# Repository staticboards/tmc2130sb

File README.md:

# TMC2130 SB

The TM2130 SB is a stepper motor driver based on the advanced TMC 2130 driver.

The TMC2130 SB is a derived work from the Silent Step Stick https://github.com/watterott/SilentStepStick. We rewrote the project using kicad, with some improvements, like the potentiometer on the upper side. This is a 4 layer board with improved heat dissipation.

* Full compatible with Pololu a4988 and DRV8825
* Compatible with SPI mode

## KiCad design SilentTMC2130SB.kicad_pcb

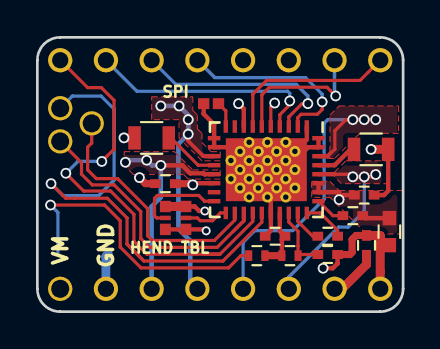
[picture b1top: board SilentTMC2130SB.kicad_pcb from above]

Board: 4 copper layers, 20.3 x 15.2 mm, 22 parts (1 on the bottom side), 28 nets.

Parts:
C1, C4, C5, C7: 100n/50V; C_0402
C2: 470n/10V; C_0402
C3: 4u7/10V; C_0402
C6: 22n/50V; C_0402
C8: 1u/50V; C_0603
J1: HEND; JUMPER3-SMD
J2: TBL; JUMPER3-SMD
J3: SPI; JUMPER_SMD
J4, J5: CONN_01X08; Pin_Header_Straight_1x08_Pitch2.54mm
J6, J7, J8: CONN_01X01; Pin_Header_Straight_1x01_Pitch1.00mm
R1: 2R2; R_0402
R2, R3: 0R; R_0805
R4: 20K; R_0402
RV1: 20K; TRIMMER-3MM-SMD
U1: TMC2130-LA; QFN-36-1EP_5x6mm_Pitch0.5mm-TERMALPADS

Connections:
+5V: C3.2, R1.1, R4.1, U1.25
A1: J5.5, U1.34
A2: J5.6, U1.32
B1: J5.4, U1.13
B2: J5.3, U1.15
CFG0: J4.4, U1.5
CFG1: J4.7, U1.4
CFG2: J4.6, U1.3
CFG3: J4.5, U1.2
CFG4: J1.3, U1.18
CFG5: J2.3, U1.19
CFG6: J4.8, U1.22
DIAG0: J6.1, U1.20
DIAG1: J7.1, U1.21
DIR: J4.1, U1.7
GND: C1.2, C2.2, C3.1, C4.2, C7.2, C8.2, J1.1, J2.2, J3.1, J5.2, J5.8, R2.1, R3.1, RV1.1, U1.1, U1.11, U1.12, U1.24, U1.35, U1.36, U1.37
IREF: J8.1, RV1.2, U1.23
unnamed: C2.1, R1.2, U1.26
unnamed: C5.2, U1.29
unnamed: C6.1, U1.28
unnamed: C6.2, U1.27
unnamed: J3.2, U1.10
unnamed: R2.2, U1.33
unnamed: R3.2, U1.14
unnamed: R4.2, RV1.3
STEP: J4.2, U1.6
VIO: C1.1, J1.2, J2.1, J5.7, U1.8
VMOT: C4.1, C5.1, C7.1, C8.1, J5.1, U1.16, U1.30, U1.31

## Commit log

2018-11-07 initial release
2018-11-07 fixed license
2018-11-07 added a quick readme
2018-11-07 fixed readme
